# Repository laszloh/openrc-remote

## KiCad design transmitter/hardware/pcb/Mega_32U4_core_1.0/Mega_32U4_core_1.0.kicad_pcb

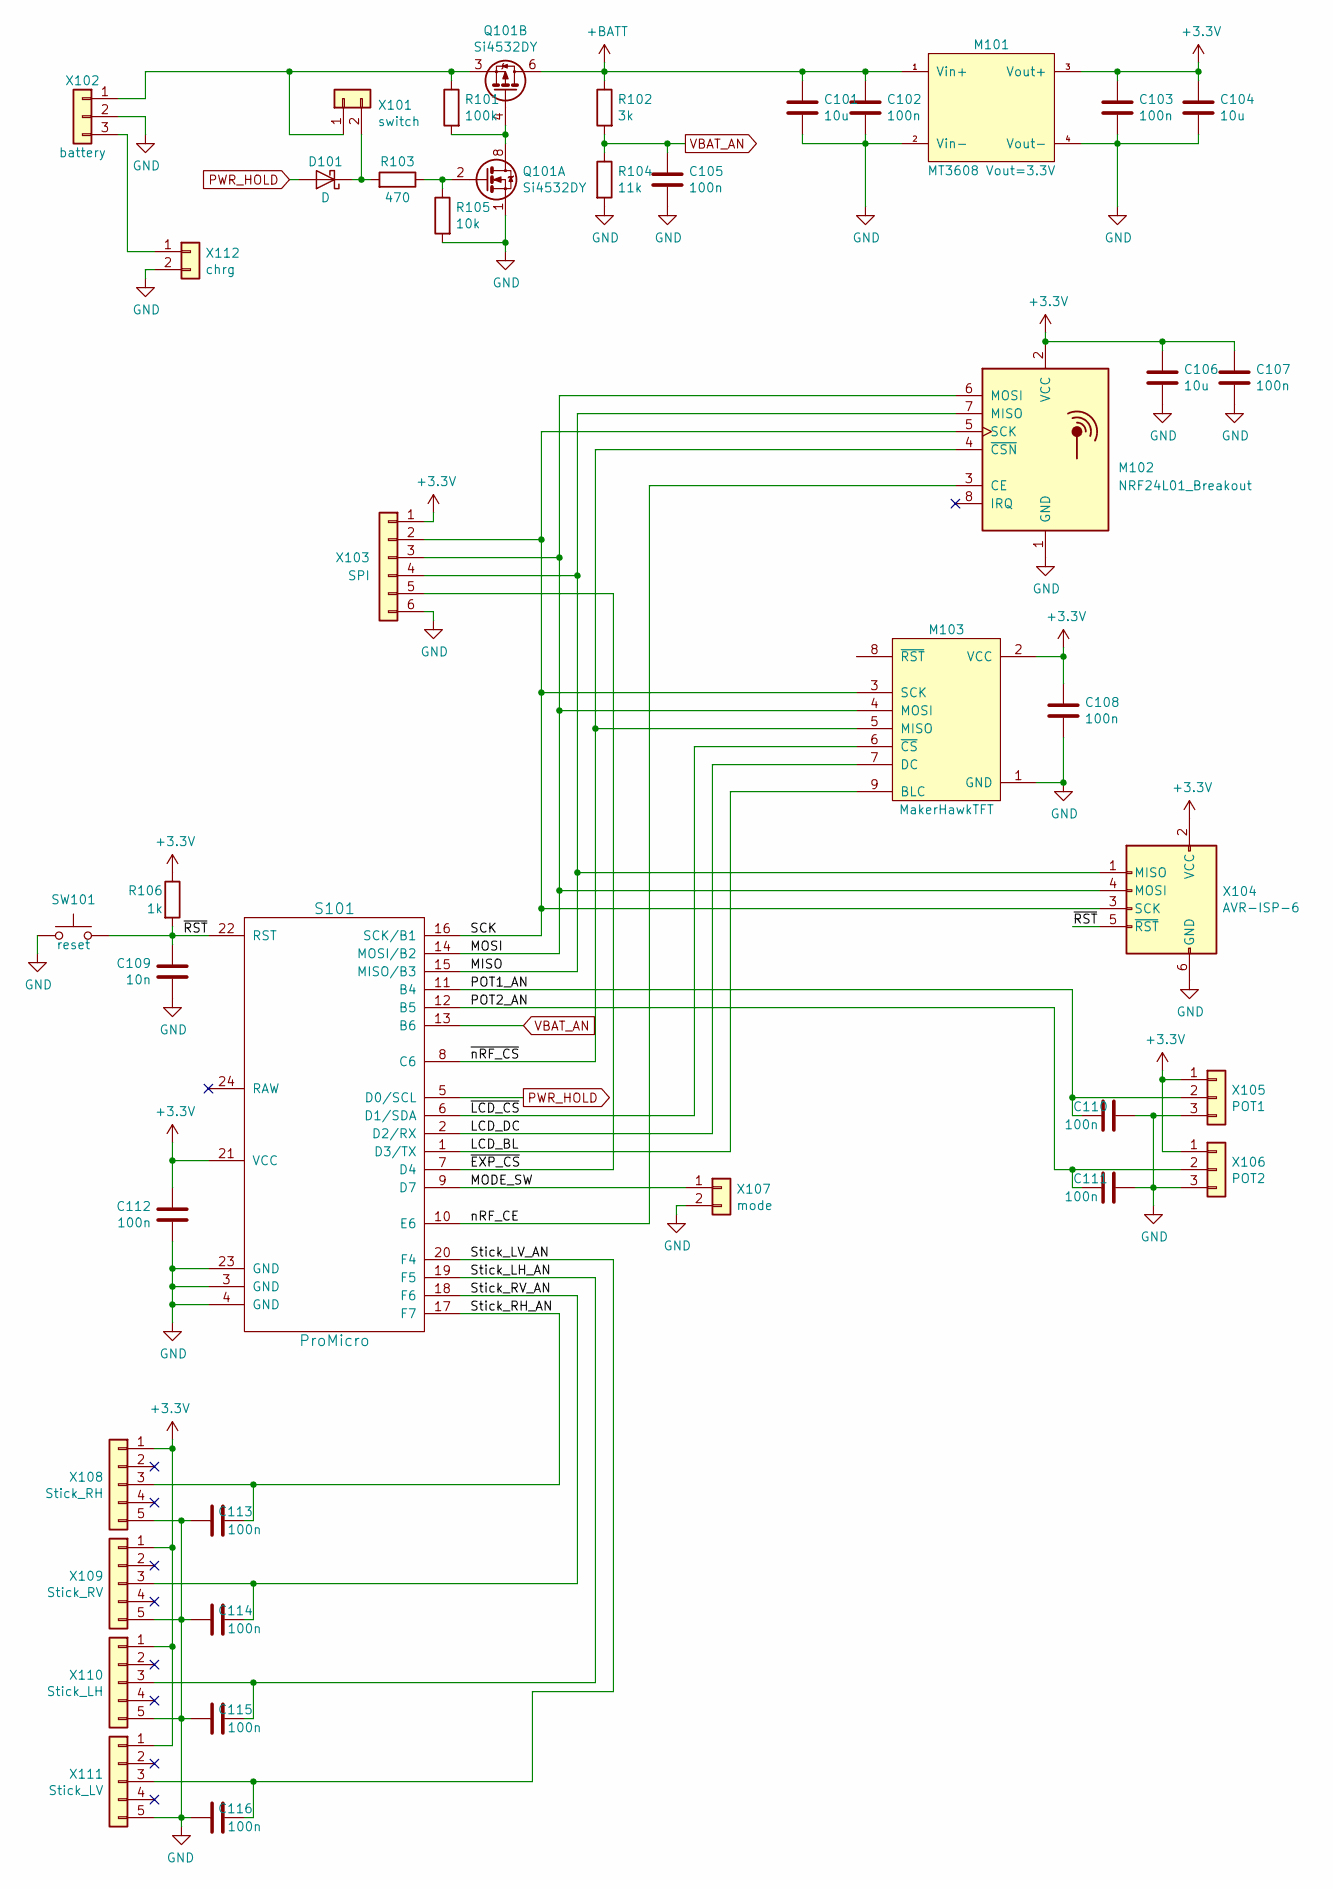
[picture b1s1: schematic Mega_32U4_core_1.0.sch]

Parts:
C101, C104, C106: 10u; C_1206_3216Metric
C102, C103, C105, C107, C108, C110, C111, C112, C113, C114, C115, C116: 100n; C_0603_1608Metric
C109: 10n; C_0603_1608Metric
D101: D; D_SMA
M101: MT3608 Vout=3.3V; MT3608_module
M102: NRF24L01_Breakout; nRF24L01_Breakout
M103: MakerHawkTFT; PinSocket_1x09_P2.54mm_Vertical
Q101: Si4532DY; SOIC-8_3.9x4.9mm_P1.27mm
R101: 100k; R_0603_1608Metric
R102: 3k; R_0603_1608Metric
R103: 470; R_0603_1608Metric
R104: 11k; R_0603_1608Metric
R105: 10k; R_0603_1608Metric
R106: 1k; R_0603_1608Metric
S101: ProMicro
SW101: reset; SW_PUSH_6mm_H4.3mm
X101: switch; PinSocket_1x02_P2.54mm_Vertical
X102: battery; Molex_KK-254_AE-6410-03A_1x03_P2.54mm_Vertical
X103: SPI; PinSocket_1x06_P2.54mm_Vertical
X104: AVR-ISP-6; PinSocket_2x03_P2.54mm_Vertical
X105: POT1; PinSocket_1x03_P2.54mm_Vertical
X106: POT2; PinSocket_1x03_P2.54mm_Vertical
X107: mode; PinSocket_1x02_P2.54mm_Vertical
X108: Stick_RH; PinSocket_1x05_P2.54mm_Vertical
X109: Stick_RV; PinSocket_1x05_P2.54mm_Vertical
X110: Stick_LH; PinSocket_1x05_P2.54mm_Vertical
X111: Stick_LV; PinSocket_1x05_P2.54mm_Vertical
X112: chrg; PinSocket_1x02_P2.54mm_Vertical

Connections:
+3V3: C103.1, C104.1, C106.1, C107.1, C108.1, C112.2, M101.3 (Vout+), M102.2 (VCC), M103.2 (VCC), R106.1, S101.21 (VCC), X103.1, X104.2 (VCC), X105.1, X106.1, X108.1, X109.1, X110.1, X111.1
+BATT: C101.1, C102.1, M101.1 (Vin+), Q101.5 (D), Q101.6 (D), R102.1
/LCD_BL: M103.9 (BLC), S101.1 (D3/TX)
/LCD_DC: M103.7 (DC), S101.2 (D2/RX)
/MISO: M102.7 (MISO), S101.15 (MISO/B3), X103.4, X104.1 (MISO)
/MODE_SW: S101.9 (D7), X107.1
/MOSI: M102.6 (MOSI), M103.4 (MOSI), S101.14 (MOSI/B2), X103.3, X104.4 (MOSI)
/POT1_AN: C110.2, S101.11 (B4), X105.2
/POT2_AN: C111.2, S101.12 (B5), X106.2
/SCK: M102.5 (SCK), M103.3 (SCK), S101.16 (SCK/B1), X103.2, X104.3 (SCK)
/Stick_LH_AN: C115.2, S101.19 (F5), X110.3
/Stick_LV_AN: C116.2, S101.20 (F4), X111.3
/Stick_RH_AN: C113.2, S101.17 (F7), X108.3
/Stick_RV_AN: C114.2, S101.18 (F6), X109.3
/nRF_CE: M102.3 (CE), S101.10 (E6)
/~EXP_CS: S101.7 (D4), X103.5
/~LCD_CS: M103.6 (~CS), S101.6 (D1/SDA)
/~RST: C109.2, R106.2, S101.22 (RST), SW101.2, X104.5 (~RST)
/~nRF_CS: M102.4 (~CSN), M103.5 (MISO), S101.8 (C6)
GND: C101.2, C102.2, C103.2, C104.2, C105.2, C106.2, C107.2, C108.2, C109.1, C110.1, C111.1, C112.1, C113.1, C114.1, C115.1, C116.1, M101.2 (Vin-), M101.4 (Vout-), M102.1 (GND), M103.1 (GND), Q101.1 (S), R104.2, R105.2, S101.3 (GND), S101.4 (GND), S101.23 (GND), SW101.1, X102.2, X103.6, X104.6 (GND), X105.3, X106.3, X107.2, X108.5, X109.5, X110.5, X111.5, X112.2
unnamed: D101.1 (K), R103.2, X101.2
unnamed: Q101.2 (G), R103.1, R105.1
unnamed: Q101.3 (1), R101.1, X101.1, X102.1
unnamed: Q101.4 (G), Q101.7 (D), Q101.8 (D), R101.2
unnamed: X102.3, X112.1
PWR_HOLD: D101.2 (A), S101.5 (D0/SCL)
VBAT_AN: C105.1, R102.2, R104.1, S101.13 (B6)

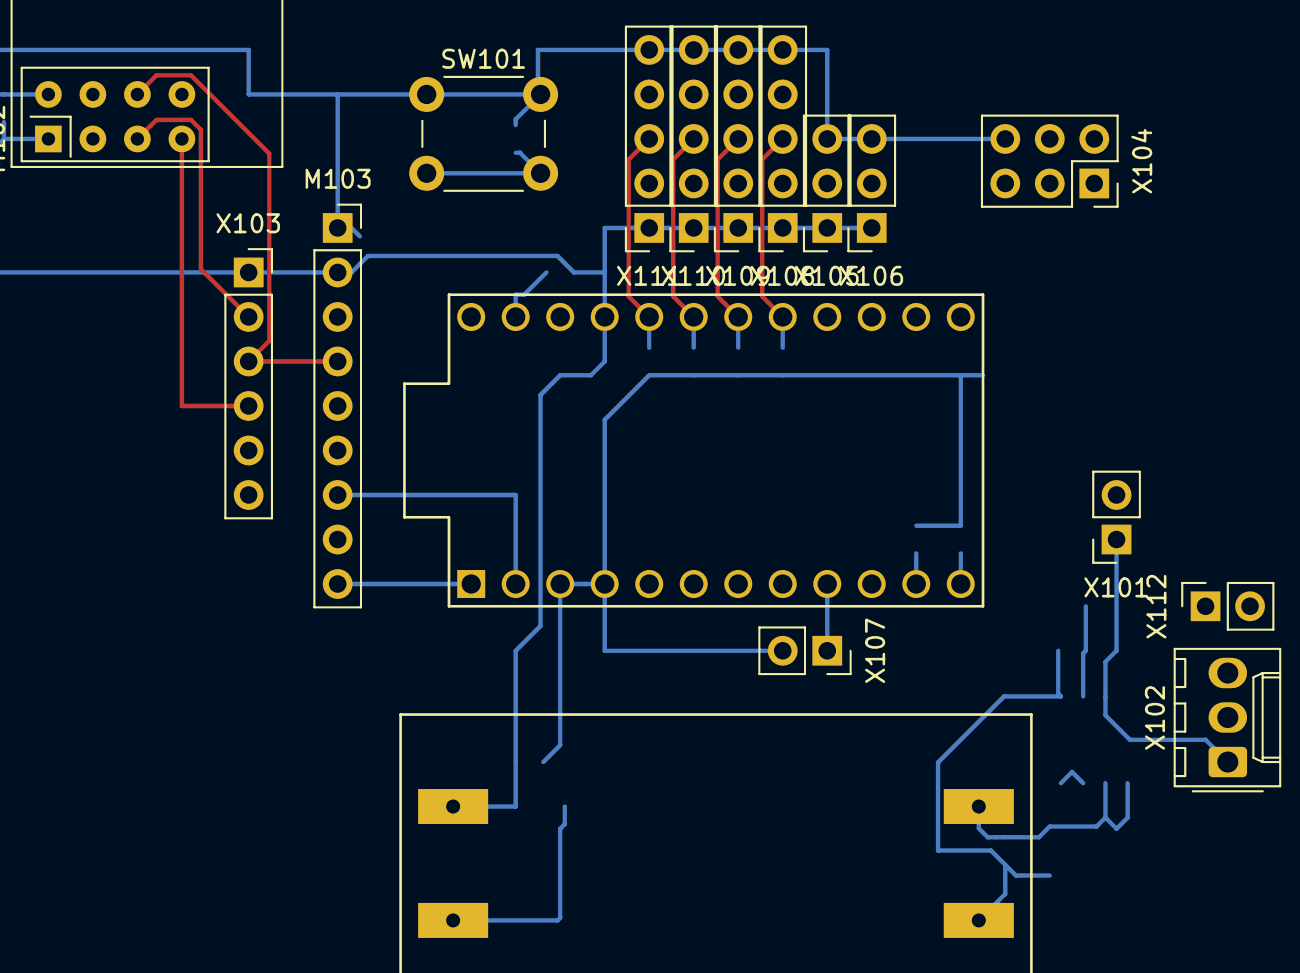
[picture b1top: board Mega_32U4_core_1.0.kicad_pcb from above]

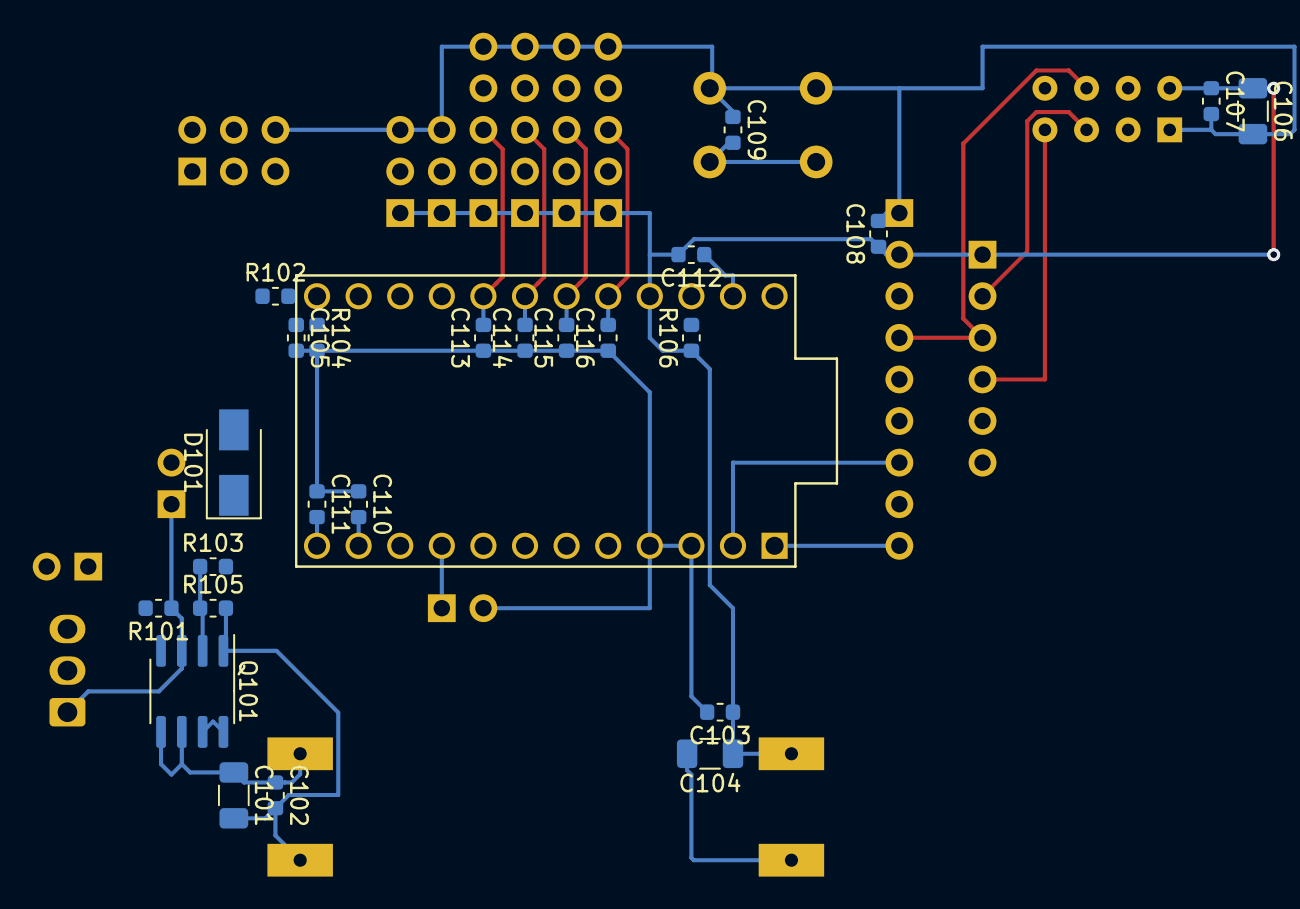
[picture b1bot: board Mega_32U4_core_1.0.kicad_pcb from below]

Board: 2 copper layers, 41 parts (24 on the bottom side), 27 nets.

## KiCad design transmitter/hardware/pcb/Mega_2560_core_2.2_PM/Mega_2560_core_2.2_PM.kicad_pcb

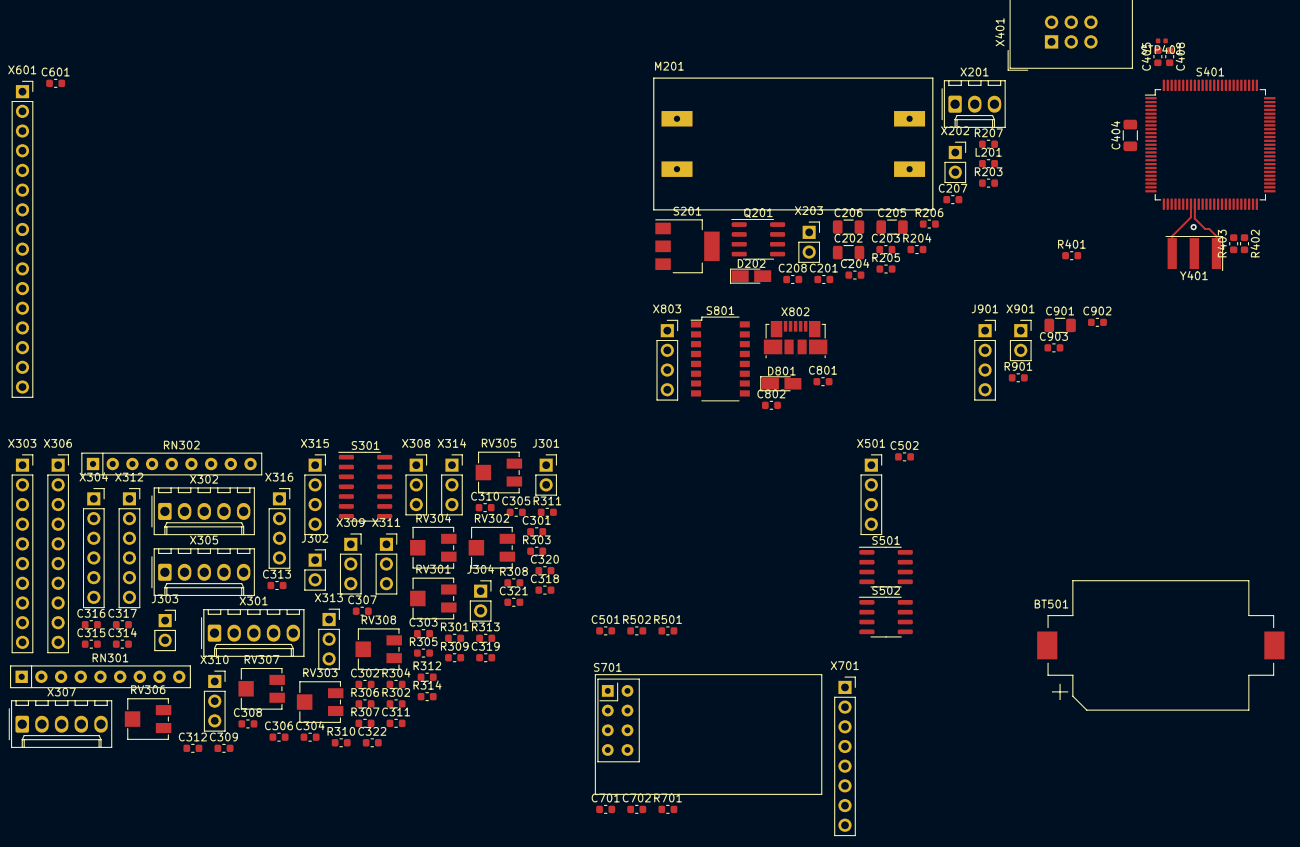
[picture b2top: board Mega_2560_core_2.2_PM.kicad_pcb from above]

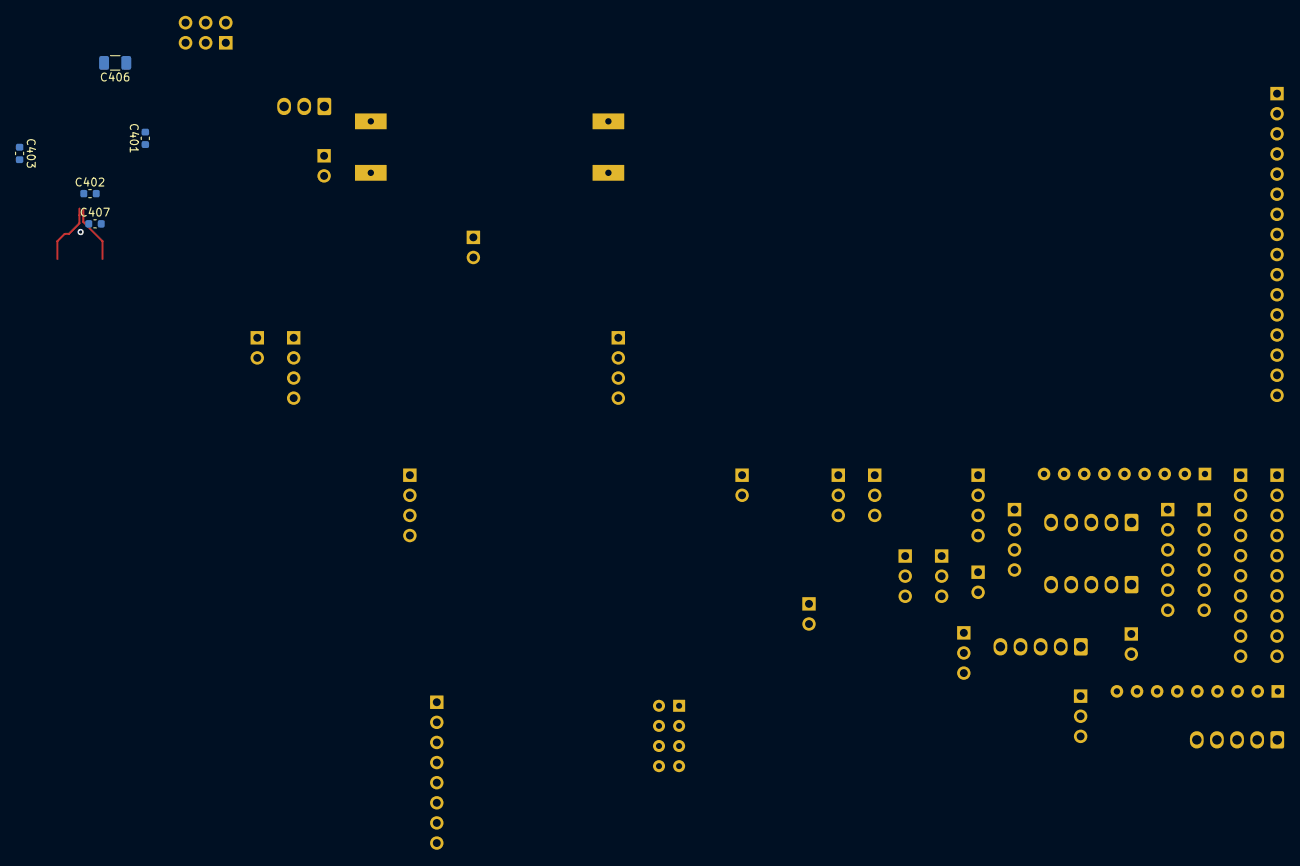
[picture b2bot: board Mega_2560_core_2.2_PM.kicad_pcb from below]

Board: 2 copper layers, 130 parts (5 on the bottom side), 112 nets.

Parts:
BT501: Battery_Cell; BatteryHolder_Keystone_1060_1x2032
C201, C203, C204, C207, C301, C302, C305, C307, C309, C310, C312, C313, C314, C315, C316, C317, C318, C319, C320, C321, C322, C401, C402, C403, C405, C408, C501, C502, C601, C701, C902, C903: 100n; C_0603_1608Metric
C202, C205, C206, C404, C406, C901: 10u; C_1206_3216Metric
C208: 100u; C_0603_1608Metric
C303: 68n; C_0603_1608Metric
C304, C306, C308, C311: 22n; C_0603_1608Metric
C407, C801, C802: 10n; C_0603_1608Metric
C702: 10u; C_0603_1608Metric
D202: D_Schottky; D_MicroMELF_Hadsoldering
D801: D; D_MicroMELF_Hadsoldering
J301, J302, J303, J304: TestPoint_2Pole; PinSocket_1x02_P2.54mm_Vertical
J901: Conn_01x04; PinSocket_1x04_P2.54mm_Vertical
L201: bead; L_0603_1608Metric
M201: MT3608_Modul; MT3608_module
Q201: Si4532DY; SOIC-8_3.9x4.9mm_P1.27mm
R203, R204, R206: 46k; R_0603_1608Metric
R205, R207: 470R; R_0603_1608Metric
R301, R306, R309, R312: 47k; R_0603_1608Metric
R302, R305: 39k; R_0603_1608Metric
R303, R307, R310, R313: 120k; R_0603_1608Metric
R304, R308, R311, R314: 68k; R_0603_1608Metric
R401, R402, R403: R; R_0603_1608Metric
R501, R502: 10k; R_0603_1608Metric
R701: 200R; R_0603_1608Metric
R901: 1k; R_0603_1608Metric
RN301, RN302: R_Network08; R_Array_SIP9
RV301, RV302, RV303, RV304, RV305, RV306, RV307, RV308: 100k; Potentiometer_Vishay_TS53YJ_Vertical
S201: AMS1117-3.3; SOT-223-3_TabPin2
S301: MCP6004; SOIC-14_3.9x8.7mm_P1.27mm
S401: ATmega2560-16AU; TQFP-100_14x14mm_P0.5mm
S501: DS3231MZ; SOIC-8_3.9x4.9mm_P1.27mm
S502: 24LC32; SOIC-8_3.9x4.9mm_P1.27mm
S701: NRF24L01_Breakout; nRF24L01_Breakout
S801: CH340G; SOP-16_4.4x10.4mm_P1.27mm
STP401: Starpoint-2; R_0402_1005Metric
X201: BATT; Molex_KK-254_AE-6410-03A_1x03_P2.54mm_Vertical
X202: switch; PinSocket_1x02_P2.54mm_Vertical
X203: charge; PinSocket_1x02_P2.54mm_Vertical
X301: Stick_RH; Molex_KK-254_AE-6410-05A_1x05_P2.54mm_Vertical
X302: Stick_RV; Molex_KK-254_AE-6410-05A_1x05_P2.54mm_Vertical
X303, X306: Trim; PinSocket_1x10_P2.54mm_Vertical
X304: buttons; PinSocket_1x06_P2.54mm_Vertical
X305: Stick_LH; Molex_KK-254_AE-6410-05A_1x05_P2.54mm_Vertical
X307: Stick_LV; Molex_KK-254_AE-6410-05A_1x05_P2.54mm_Vertical
X308: Pot1; PinSocket_1x03_P2.54mm_Vertical
X309: Pot2; PinSocket_1x03_P2.54mm_Vertical
X310: Pot3; PinSocket_1x03_P2.54mm_Vertical
X311: Pot4; PinSocket_1x03_P2.54mm_Vertical
X312: 3-way sw; PinSocket_1x06_P2.54mm_Vertical
X313: Pot5; PinSocket_1x03_P2.54mm_Vertical
X314: Pot6; PinSocket_1x03_P2.54mm_Vertical
X315: encoder 1; PinSocket_1x04_P2.54mm_Vertical
X316: encoder 2; PinSocket_1x04_P2.54mm_Vertical
X401: AVR-ISP-6; IDC-Header_2x03_P2.54mm_Vertical
X501: I2C; PinSocket_1x04_P2.54mm_Vertical
X601: 3.5'' LCD; PinSocket_1x16_P2.54mm_Vertical
X701: Conn_01x08; PinSocket_1x08_P2.54mm_Vertical
X802: USB_OTG; USB_Micro-B_Molex_47346-0001
X803: Serial; PinSocket_1x04_P2.54mm_Vertical
X901: buzzer; PinSocket_1x02_P2.54mm_Vertical
Y401: 16MHz; Resonator_SMD_muRata_SFECV-3Pin_6.9x2.9mm

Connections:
+2V5: C303.2, R302.1, R305.2, S301.3, S301.5, S301.10, S301.12
+3V3: C206.1, C207.1, C601.1, C701.1, C702.1, S201.2, S701.2
+5C: X201.3, X203.1
+5V: C204.1, C205.1, C401.2, C402.2, C403.2, C404.2, C501.1, C502.1, C801.2, C901.1, C902.1, D801.1, L201.2, M201.3, R401.2, R402.2, R403.1, R501.1, R502.1, S201.3, S401.10, S401.31, S401.61, S401.80, S501.2, S502.8, S801.16, X401.2, X501.1, X601.1, X601.10, X701.2, X803.1
+5VA: C201.1, C302.2, C405.1, C406.1, L201.1, R302.2, RN301.1, RV302.1, RV304.1, RV306.1, RV308.1, S301.4, S401.100, X301.1, X302.1, X305.1, X307.1, X308.1, X309.1, X310.1, X311.1, X312.1, X313.1, X314.1
+BATT: C202.1, C203.1, C208.1, C903.2, J901.3, M201.1, Q201.5, Q201.6, R203.2, X701.1
/OpenAVRc_Comm/MISO: S401.22, S701.7, X401.1
/OpenAVRc_Comm/MOSI: S401.21, S701.6, X401.4
/OpenAVRc_Comm/Module_PPM: R701.2, S401.5
/OpenAVRc_Comm/Module_RX: S401.64, X701.5
/OpenAVRc_Comm/Module_SimControl: S401.49, X701.8
/OpenAVRc_Comm/Module_TX: S401.63, X701.7
/OpenAVRc_Controller/PB0\~SS~\PCINT0: C321.2, S401.19, X316.2
/OpenAVRc_Controller/PB1\SCK\PCINT1: S401.20, S701.5, X401.3
/OpenAVRc_Controller/PB4\OC2A\PCINT4: C320.2, S401.23, X316.3
/OpenAVRc_Controller/PB5\OC1A\PCINT5: C319.2, S401.24, X315.1
/OpenAVRc_Controller/PB6\OC1B\PCINT6: C318.2, S401.25, X315.2
/OpenAVRc_Controller/PB7\OC0A\OC1C\PCINT7: C317.2, S401.26, X315.3
/OpenAVRc_Controller/PC0: S401.53, X303.1
/OpenAVRc_Controller/PC1: S401.54, X303.2
/OpenAVRc_Controller/PC2: S401.55, X303.3
/OpenAVRc_Controller/PC3: S401.56, X303.4
/OpenAVRc_Controller/PC4: S401.57, X303.5
/OpenAVRc_Controller/PC5: S401.58, X303.6
/OpenAVRc_Controller/PC6: S401.59, X303.7
/OpenAVRc_Controller/PC7: S401.60, X303.8
/OpenAVRc_Controller/PD0\~INT0~\SCL: R403.2, S401.43, S501.8, S502.6, X501.3
/OpenAVRc_Controller/PD1\~INT1~\SDA: R402.1, S401.44, S501.7, S502.5, X501.2
/OpenAVRc_Controller/PD2\~INT2~\RXD1: S401.45, X803.3
/OpenAVRc_Controller/PD3\~INT3~\TXD1: S401.46, X803.2
/OpenAVRc_Controller/PD4\ICP1: S401.47, S701.4
/OpenAVRc_Controller/PD5\XCK1: S401.48, S701.3
/OpenAVRc_Controller/PD7\T0: S401.50, X306.8
/OpenAVRc_Controller/PE0\RXD0\PCINT8: S401.2, S801.2
/OpenAVRc_Controller/PE1\TXD0: S401.3, S801.3
/OpenAVRc_Controller/PE5\INT5\OC3C: R502.2, S401.7, S501.3
/OpenAVRc_Controller/PF0\ADC0: C311.1, J304.2, RV307.1, RV307.2, S301.14, S401.97
/OpenAVRc_Controller/PF1\ADC1: C308.1, J303.2, RV305.1, RV305.2, S301.8, S401.96
/OpenAVRc_Controller/PF2\ADC2: C306.1, J302.2, RV303.1, RV303.2, S301.7, S401.95
/OpenAVRc_Controller/PF3\ADC3: C304.1, J301.2, RV301.1, RV301.2, S301.1, S401.94
/OpenAVRc_Controller/PF4\ADC4\TCK: C310.1, S401.93, X308.2
/OpenAVRc_Controller/PF5\ADC5\TMS: C312.1, S401.92, X309.2
/OpenAVRc_Controller/PF6\ADC6\TDO: C313.1, S401.91, X310.2
/OpenAVRc_Controller/PG0: S401.51, X306.1
/OpenAVRc_Controller/PG1: S401.52, X306.2
/OpenAVRc_Controller/PG2: S401.70, X306.3
/OpenAVRc_Controller/PG3\TOSC2: S401.28, X306.4
/OpenAVRc_Controller/PG4\TOSC1: S401.29, X306.5
/OpenAVRc_Controller/PG5\OC0B: S401.1, X306.6
/OpenAVRc_Controller/PH1\TXD2: R901.1, S401.13
/OpenAVRc_Controller/PH7\T4: S401.27, X306.7
/OpenAVRc_Controller/PJ2\XCK3\PCINT11: S401.65, X304.1
/OpenAVRc_Controller/PJ3\PCINT12: S401.66, X304.2
/OpenAVRc_Controller/PJ4\PCINT13: S401.67, X304.3
/OpenAVRc_Controller/PJ5\PCINT14: S401.68, X304.4
/OpenAVRc_Controller/PJ6\PCINT15: S401.69, X304.5
/OpenAVRc_Controller/PK0\ADC8\PCINT16: RN301.2, RN302.2, S401.89, X312.2
/OpenAVRc_Controller/PK1\ADC9\PCINT17: RN301.3, RN302.3, S401.88, X312.3
/OpenAVRc_Controller/PK2\ADC10\PCINT17: RN301.4, RN302.4, S401.87, X312.4
/OpenAVRc_Controller/PK3\ADC11\PCINT19: RN301.5, RN302.5, S401.86, X312.5
/OpenAVRc_Controller/PK4\ADC12\PCINT20: C322.2, S401.85, X316.1
/OpenAVRc_Controller/PK5\ADC13\PCINT21: C314.1, S401.84, X311.2
/OpenAVRc_Controller/PK6\ADC14\PCINT22: C315.1, S401.83, X313.2
/OpenAVRc_Controller/PK7\ADC15\PCINT23: C316.1, S401.82, X314.2
/OpenAVRc_Controller/PL7: D202.2, S401.42
/OpenAVRc_Controller/~RESET: C407.2, R401.1, S401.30, X401.5
/OpenAVRc_Display/LCD_CS: S401.41, X601.12
/OpenAVRc_Display/LCD_D0: S401.78, X601.2
/OpenAVRc_Display/LCD_D1: S401.77, X601.3
/OpenAVRc_Display/LCD_D2: S401.76, X601.4
/OpenAVRc_Display/LCD_D3: S401.75, X601.5
/OpenAVRc_Display/LCD_D4: S401.74, X601.6
/OpenAVRc_Display/LCD_D5: S401.73, X601.7
/OpenAVRc_Display/LCD_D6: S401.72, X601.8
/OpenAVRc_Display/LCD_D7: S401.71, X601.9
/OpenAVRc_Display/LCD_RS: S401.79, X601.13
/OpenAVRc_Display/LCD_WR: S401.37, X601.11
/OpenAVRc_Feedback/Buzzer: J901.1, S401.15
/OpenAVRc_Power/BAT_VSENSE: R203.1, R206.2, S401.90
GND: BT501.2, C201.2, C202.2, C203.2, C204.2, C205.2, C206.2, C207.2, C208.2, C317.1, C318.1, C319.1, C320.1, C321.1, C322.1, C401.1, C402.1, C403.1, C404.1, C407.1, C501.2, C502.2, C601.2, C701.2, C702.2, C801.1, C802.1, C901.2, C902.2, C903.1, J901.4, M201.2, M201.4, Q201.1, R206.1, S201.1, S401.11, S401.32, S401.62, S401.81, S401.99, S501.5, S502.1, S502.2, S502.3, S502.4, S502.7, S701.1, S801.1, STP401.1, X201.2, X203.2, X303.9, X303.10, X304.6, X306.9, X306.10, X315.4, X316.4, X401.6, X501.4, X601.15, X601.16, X701.3, X701.6, X802.5, X802.6, X803.4, Y401.2
GNDA: C301.2, C302.1, C303.1, C305.2, C307.2, C309.2, C310.2, C312.2, C313.2, C314.2, C315.2, C316.2, C405.2, C406.2, C408.1, R305.1, RN302.1, RV302.3, RV304.3, RV306.3, RV308.3, S301.11, STP401.2, X301.5, X302.5, X305.5, X307.5, X308.3, X309.3, X310.3, X311.3, X312.6, X313.3, X314.3
unnamed: BT501.1, S501.6
unnamed: C301.1, R301.2, X301.3
unnamed: C304.2, J301.1, R301.1, R303.2, R304.1, S301.2
unnamed: C305.1, R306.2, X302.3
unnamed: C306.2, J302.1, R306.1, R307.2, R308.1, S301.6
unnamed: C307.1, R309.2, X305.3
unnamed: C308.2, J303.1, R309.1, R310.2, R311.1, S301.9
unnamed: C309.1, R312.2, X307.3
unnamed: C311.2, J304.1, R312.1, R313.2, R314.1, S301.13
unnamed: C408.2, S401.98
unnamed: C802.2, S801.4
unnamed: D202.1, R207.2
unnamed: D801.2, X802.1
unnamed: Q201.2, R205.1, R207.1
unnamed: Q201.3, R204.2, X201.1, X202.1
unnamed: Q201.4, Q201.7, Q201.8, R204.1
unnamed: R205.2, X202.2
unnamed: R303.1, RV302.2
unnamed: R304.2, RV301.3
unnamed: R307.1, RV304.2
unnamed: R308.2, RV303.3
unnamed: R310.1, RV306.2
unnamed: R311.2, RV305.3
unnamed: R313.1, RV308.2
unnamed: R314.2, RV307.3
unnamed: R501.2, S501.1
unnamed: R701.1, X701.4
unnamed: S401.33, Y401.3
unnamed: S401.34, Y401.1
unnamed: S801.5, X802.3
unnamed: S801.6, X802.2

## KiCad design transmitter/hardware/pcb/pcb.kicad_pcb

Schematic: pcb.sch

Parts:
C101, C102, C105, C108: 10u; C_1206_3216Metric
C103, C104, C106, C107, C109, C110, C111, C112: 100n; C_0805_2012Metric_Pad1.15x1.40mm_HandSolder
M101: MT3608_Modul; MT3608_module
P101, P102, P103, P104, P105, P106, P107, P108, P109, P110, P111, P112, P113, P114, P115, P116, P117, P118, P119, P120, P121, P122, P123, P124, P125, P126, P127, P128, P129, P130, P131, P132, P133, P134, P135, P136, P137, P138, P139, P140, P141: TestPoint_Alt; TestPoint_Pad_D1.0mm
Q101: BC847; SOT-23
R101, R104, R105, R106, R107, R108, R109, R110, R111, R112, R113, R114, R115, R116, R117, R118, R119: 1k; R_0603_1608Metric
R102: n.b.; R_0603_1608Metric
R103: 2k; R_0603_1608Metric
S101: AMS1117-3.3; SOT-223-3_TabPin2
S102: NRF24L01_Breakout; nRF24L01_Breakout
S103: ProMicro
S104, S106: 74HC165; SOIC-16_3.9x9.9mm_P1.27mm
S105: 74AHC1G125; SOT-353_SC-70-5
SW101: POWER; SW_Graupner_JS202011AQN_DPDT_Angled
SW102: ~RST; SW_Tactile_SPST_Angled_PTS645Vx39-2LFS
X101: power; Molex_KK-254_AE-6410-02A_1x02_P2.54mm_Vertical
X102: Display; PinHeader_1x09_P2.54mm_Vertical
X103: UART; PinHeader_1x04_P2.54mm_Vertical
X104: gimbal_left_h; PinSocket_1x03_P2.54mm_Vertical
X105: gimbal_left_v; PinSocket_1x03_P2.54mm_Vertical
X106: gimbal_right_h; PinSocket_1x03_P2.54mm_Vertical
X107: gimbal_right_v; PinSocket_1x03_P2.54mm_Vertical
X108: switches_1; PinHeader_2x08_P2.54mm_Vertical
X109: switches_2; PinHeader_2x08_P2.54mm_Vertical
X110: chrg_out; SolderWirePad_1x01_Drill1.2mm
XA02: charge; BarrelJack_Horizontal

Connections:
+5C: X110.1, XA02.1
+5V: C102.1, C103.1, C107.1, C108.1, C109.1, C110.1, C111.1, C112.1, M101.3 (Vout+), P101.1, R104.1, R105.1, R106.1, R107.1, R108.1, R109.1, R110.1, R111.1, R112.1, R113.1, R114.1, R115.1, R116.1, R117.1, R118.1, R119.1, S101.3 (VI), S103.21 (VCC), S104.16, S105.5 (VCC), S106.16, X102.2, X102.8, X103.1, X104.1, X105.1, X106.1, X107.1
+BATT: C101.1, M101.1 (Vin+), R101.1, SW101.1
/GIMBAL_LEFT_H: P120.1, S103.20 (F4), X104.2
/GIMBAL_LEFT_V: P121.1, S103.19 (F5), X105.2
/GIMBAL_RIGHT_H: P122.1, S103.18 (F6), X106.2
/GIMBAL_RIGHT_V: P123.1, S103.17 (F7), X107.2
/IRQ: P108.1, S102.8 (IRQ)
/LCD_BL: P118.1, Q101.1 (B), S103.6 (D1/SDA)
/LCD_DC: P111.1, S103.5 (D0/SCL), X102.4
/MISO: P105.1, R103.1, S102.7 (MISO), S103.15 (MISO/B3), S105.4
/MOSI: P112.1, S102.6 (MOSI), S103.14 (MOSI/B2), X102.5
/NRF24_CE: P107.1, S102.3 (CE), S103.12 (B5)
/PE_LATCH: P119.1, S103.10 (E6), S104.1, S106.1
/RX: P116.1, S103.2 (D2/RX), X103.2
/S104_SOUT: P132.1, S104.9, S106.10
/SCK: P113.1, S102.5 (SCK), S103.16 (SCK/B1), S104.2, S106.2, X102.6
/SW1: P124.1, R104.2, S104.11, X108.2
/SW2: P125.1, R106.2, S104.12, X108.4
/SW3: P126.1, R108.2, S104.13, X108.6
/SW4: P127.1, R110.2, S104.14, X108.8
/SW5: P128.1, R112.2, S104.3, X108.10
/SW6: P129.1, R114.2, S104.4, X108.12
/SW7: P130.1, R116.2, S104.5, X108.14
/SW8: P131.1, R118.2, S104.6, X108.16
/SW9: P133.1, R105.2, S106.11, X109.2
/SW10: P138.1, R107.2, S106.12, X109.4
/SW11: P134.1, R109.2, S106.13, X109.6
/SW12: P139.1, R111.2, S106.14, X109.8
/SW13: P135.1, R113.2, S106.3, X109.10
/SW14: P140.1, R115.2, S106.4, X109.12
/SW15: P137.1, R117.2, S106.5, X109.14
/SW16: P141.1, R119.2, S106.6, X109.16
/TX: P117.1, S103.1 (D3/TX), X103.3
/VBAT_ADC: R101.2, R102.1, S103.7 (D4)
/~LCD_CS: P114.1, S103.13 (B6), X102.7
/~LCD_RST: P110.1, S103.8 (C6), X102.3
/~NRF24_CS: P106.1, S102.4 (~CSN), S103.11 (B4)
/~PE_CS: P115.1, S103.9 (D7), S104.15, S105.1, S106.15
/~RST: P109.1, S103.22 (RST), SW102.1
GND: C101.2, C102.2, C103.2, C104.2, C105.2, C106.2, C107.2, C108.2, C109.2, C110.2, C111.2, C112.2, M101.2 (Vin-), M101.4 (Vout-), P104.1, Q101.2 (E), R102.2, S101.1 (GND), S102.1 (GND), S103.3 (GND), S103.4 (GND), S103.23 (GND), S104.8, S105.3 (GND), S106.8, SW102.2, X101.2, X102.1, X103.4, X104.3, X105.3, X106.3, X107.3, X108.1, X108.3, X108.5, X108.7, X108.9, X108.11, X108.13, X108.15, X109.1, X109.3, X109.5, X109.7, X109.9, X109.11, X109.13, X109.15, XA02.2
unnamed: P103.1, SW101.2, X101.1
unnamed: P136.1, R103.2, S105.2, S106.9
unnamed: Q101.3 (C), X102.9

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
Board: 2 copper layers, 93 parts (18 on the bottom side), 45 nets, no tracks yet.

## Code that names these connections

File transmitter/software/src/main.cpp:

/**
 * @file main.cpp
 * @author Laszlo Hegedüs (laszlo.hegedues@gmail.com)
 * @brief
 * @version 0.1
 * @date 2019-05-10
 *
 * @copyright Copyright (c) 2019
 *
 * This program is free software: you can redistribute it and/or modify
 * it under the terms of the GNU General Public License as published by
 * the Free Software Foundation, either version 3 of the License, or
 * (at your option) any later version.
 *
 * This program is distributed in the hope that it will be useful,
 * but WITHOUT ANY WARRANTY; without even the implied warranty of
 * MERCHANTABILITY or FITNESS FOR A PARTICULAR PURPOSE.  See the
 * GNU General Public License for more details.
 *
 * You should have received a copy of the GNU General Public License
 * along with this program.  If not, see <http://www.gnu.org/licenses/>.
 *
 */

#include <Arduino.h>
#include <SPI.h>
#include <FastADC.h>
#include <ButtonDebouncer.h>
#include <RF24.h>
#include <avr/power.h>
#include <avr/sleep.h>

#include "AnalogButtons.h"
#include "EepromSettings.h"
#include "LcdHandler.h"

#define DEBUG

// Hardware config
// ATMEL ATMEGA32U4 / ARDUINO LEONARDO
//
// D0               PD2                 RXD1/INT2
// D1               PD3                 TXD1/INT3
// D2               PD1     SDA         SDA/INT1
// D3#              PD0     PWM8/SCL    OC0B/SCL/INT0
// D4       A6      PD4                 ADC8
// D5#              PC6     ???         OC3A/#OC4A
// D6#      A7      PD7     FastPWM     #OC4D/ADC10
// D7               PE6                 INT6/AIN0
//
// D8       A8      PB4                 ADC11/PCINT4
// D9#      A9      PB5     PWM16       OC1A/#OC4B/ADC12/PCINT5
// D10#     A10     PB6     PWM16       OC1B/0c4B/ADC13/PCINT6
// D11#             PB7     PWM8/16     0C0A/OC1C/#RTS/PCINT7
// D12      A11     PD6                 T1/#OC4D/ADC9
// D13#             PC7     PWM10       CLK0/OC4A
//
// A0       D18     PF7                 ADC7
// A1       D19     PF6                 ADC6
// A2       D20     PF5                 ADC5
// A3       D21     PF4                 ADC4
// A4       D22     PF1                 ADC1
// A5       D23     PF0                 ADC0
//
// New pins D14..D17 to map SPI port to digital pins
//
// MISO     D14     PB3                 MISO,PCINT3
// SCK      D15     PB1                 SCK,PCINT1
// MOSI     D16     PB2                 MOSI,PCINT2
// SS       D17     PB0                 RXLED,SS/PCINT0
//
// Connected LEDs on board for TX and RX
// TXLED    D30     PD5                 XCK1
// RXLED    D17     PB0
// HWB              PE2                 HWB

#define LCD_CS 10
#define LCD_DC 3
#define LCD_BL 2
#define LCD_RST 5

#define RF24_CE 9
#define RF24_CS 8

#define PE_LATCH 7
#define PE_CS 6

#define EEPROM_ADDR 0x00

#define H_LEFT_MUX 0x04   // ADC4
#define V_LEFT_MUX 0x05   // ADC5
#define H_RIGHT_MUX 0x06  // ADC6
#define V_RIGHT_MUX 0x07  // ADC7
#define VBAT_MUX 0x80     // ADC8

// Hardware configuration
RF24 radio(RF24_CE, RF24_CS);
FastADC(analog, 5, 4, true);
ButtonDebouncer(debounce, uint16_t, 8, ~0x00);
LcdHandler lcd(LCD_CS, LCD_DC, LCD_RST, LCD_BL);
Settings settings;

// Message structure
typedef struct {
  uint8_t x_axis_left;
  uint8_t y_axis_left;
  uint8_t x_axis_right;
  uint8_t y_axis_right;
  uint8_t buttons1;
  uint8_t buttons2;
} data_t;

typedef struct {
  uint16_t retry_counter;
  data_t data;
} packet_t;

// Function prototypes
static void TaskRadio();
static void enter_sleep(void);
static uint16_t read_port_expander(void);

static uint16_t get_seed(void) {
  uint16_t seed = 0;
  uint16_t *p   = (uint16_t *)(RAMEND + 1);
  extern uint16_t __heap_start;

  while (p >= &__heap_start + 1)
    seed ^= *(--p);

  return seed;
}

void setup() {
  // FastADC channel setup
  analog.reference(H_LEFT_MUX, DEFAULT);  // horizontal left stick
  analog.reference(V_LEFT_MUX, DEFAULT);  // vertical left stick
  analog.reference(H_RIGHT_MUX, DEFAULT); // horizontal right stick
  analog.reference(V_RIGHT_MUX, DEFAULT); // veritcal right stick
  analog.reference(VBAT_MUX, DEFAULT);    // battery voltage

  // load eeprom settings
  settings.loadSettings();
  if (settings.defaultSettings) {
    // default settings were loaded, create a valid unique address
    randomSeed(get_seed());
    for (uint8_t i = 0; i < sizeof(settings.rf24_addr); i++) {
      settings.rf24_addr[i] = random(UINT8_MAX);
    }
    settings.saveSettings();
  }

  // RF24 setup
  radio.begin();
  radio.setPALevel(RF24_PA_MAX);
  radio.setDataRate(RF24_250KBPS);
  radio.setChannel(settings.rf24_channel);
  radio.enableAckPayload();
  radio.enableDynamicPayloads();
  radio.openWritingPipe(settings.rf24_addr);

  // Port expander
  pinMode(PE_LATCH, OUTPUT);
  digitalWrite(PE_LATCH, LOW);

  pinMode(PE_CS, OUTPUT);
  digitalWrite(PE_CS, HIGH);

  // TFT setup
  lcd.init();

  // disable unused modules
  power_twi_disable();
#ifndef DEBUG
  power_usart1_disable();
#endif
  power_usb_disable();
  //  power_timer0_disable();
  //  power_timer1_disable();
  power_timer2_disable();
  power_timer3_disable();
  MCUCR |= _BV(JTD);
  ACSR &= ~_BV(ACIE);
  ACSR |= _BV(ACD);
}

/********************** Main Loop *********************/
void loop() {
  // debounce the buttons
  debounce.ButtonProcess(read_port_expander());

  // calling all task
  TaskRadio();
  lcd.TaskLcd();

  // we have reached the end of all tasks, go to sleep
  enter_sleep();
}

void TaskRadio(void) // This is a task.
{
  static uint8_t buffer[32];
  static uint32_t last_millis = millis();
  static packet_t packet;
  const uint16_t txIntervall = 10; // ms

  if (millis() > (last_millis + txIntervall)) {
    last_millis = millis();

    // prepare packet
    packet.data.x_axis_left  = (analog.read(H_LEFT_MUX) >> 2);
    packet.data.y_axis_left  = (analog.read(V_LEFT_MUX) >> 2);
    packet.data.x_axis_right = (analog.read(H_RIGHT_MUX) >> 2);
    packet.data.y_axis_right = (analog.read(V_RIGHT_MUX) >> 2);
    packet.data.buttons1     = debounce.ButtonPressed(0xFF);
    packet.data.buttons2     = 0x00;

    radio.powerUp();
    if (!radio.write(&packet, sizeof(packet_t))) {
      // transmission failed, increment failed counter
      packet.retry_counter++;
    } else {
      if (radio.isAckPayloadAvailable()) {
        radio.read(&buffer, sizeof(buffer));
      }
    }
    radio.powerDown();
  }
}

static void enter_sleep(void) {
  set_sleep_mode(SLEEP_MODE_IDLE);

  ATOMIC_BLOCK(ATOMIC_RESTORESTATE) {
    sleep_enable();

// Only if there is support to disable the brown-out detection.
#if defined(BODS) && defined(BODSE)
    sleep_bod_disable();
#endif
  }
  sleep_cpu(); // good night.

  // Ugh. I've been woken up. Better disable sleep mode.
  sleep_disable();
}

static uint16_t read_port_expander(void) {
  uint16_t retVal;

  digitalWrite(PE_LATCH, LOW);
  _delay_us(5);
  digitalWrite(PE_LATCH, HIGH);
  _delay_us(10);

  SPI.beginTransaction(SPISettings(4000000U, MSBFIRST, SPI_MODE0));
  digitalWrite(PE_CS, LOW);
  retVal = SPI.transfer16(0x00);
  digitalWrite(PE_CS, HIGH);
  SPI.endTransaction();

  return retVal;
}

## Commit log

2019-05-10 Initial commit
    Add all needed files and the current state of the software development
2019-05-11 Work on schematics started
    Started the work on the schematics for the transmitter part
2019-05-13 WIP on the SW parts
2019-05-15 Update code style to LLVM
2019-05-15 Add FastIO from Marlin
2019-05-28 WIP commit
2019-05-31 WIP commit for merging
2019-06-07 update pinout to new schematic
2019-06-07 add dc jack for charger connection
2019-06-14 Remove unused analog buttons
2019-06-28 Swap to atmega2560 as core
    Swap to atmega2560 as core for the remote and OpenAVRc as software
    basis.
